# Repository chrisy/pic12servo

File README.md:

pic12servo
==========

This is a simple program to drive a hobby servo with a PIC12F683. It was
prepared using the MPLAB X IDE and the xc8 compiler.

The code sets up an analog-to-digital convertor input on pin 7 and
a PWM output on pin 5. It also sets up pulse outputs on pins 2 and 3
to allow us to measure the loop timing on an oscilloscope. The output
on pin 2 should be slow enough for a blinking LED.

The program loops reading the 10-bit value from the ADC and sets the
duty cycle of the PWM to a value derived from it.

The usable range for most servos requires a pulse length of between
about 1ms to 2ms (which represents the full range of motion for the
servo) with an overall pulse rate greater than 50Hz. This program
configures the PWM output to something close to 61Hz and calculates
the duty cycle value to correspond to a pulse of between about 1 and
2ms.

By hooking up a simple 10K ohm linear potentiometer wiper to pin 7,
with the pot ends across 0v and Vdd (the positive power to the PIC,
for example 5v) then the relative position of the pot will represent
the relative position of the servo motor across its full range.

Suitable hardware designs to facilitate this are in the hardware
directory.

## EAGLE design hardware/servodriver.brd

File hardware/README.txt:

The ServoDriver hardware
========================

servodriver.sch and servodriver.brd are Eagle diagrams.

servodriver.*.tap are G-Code CAM scripts generated using gcode-pcb.ulp.

Bill of Materials
=================

IC1		PIC12F683P (programmed, with 8 pin IC socket)
IC2		7805

R1		10K Pot
R2		Link
R3		620R
R4		620R

C1		0.1uF
C2		0.1uF
C3		0.1uF
C4		100uF electrolytic (25V or higher)
C5		10uF electrolytic (10V or higher)
C6		0.1uF

D1		1N4004

LED1	3mm red LED
LED2	3mm red LED

JP1		2-way Screw terminal
JP2		3-way 0.1" pitch pin header

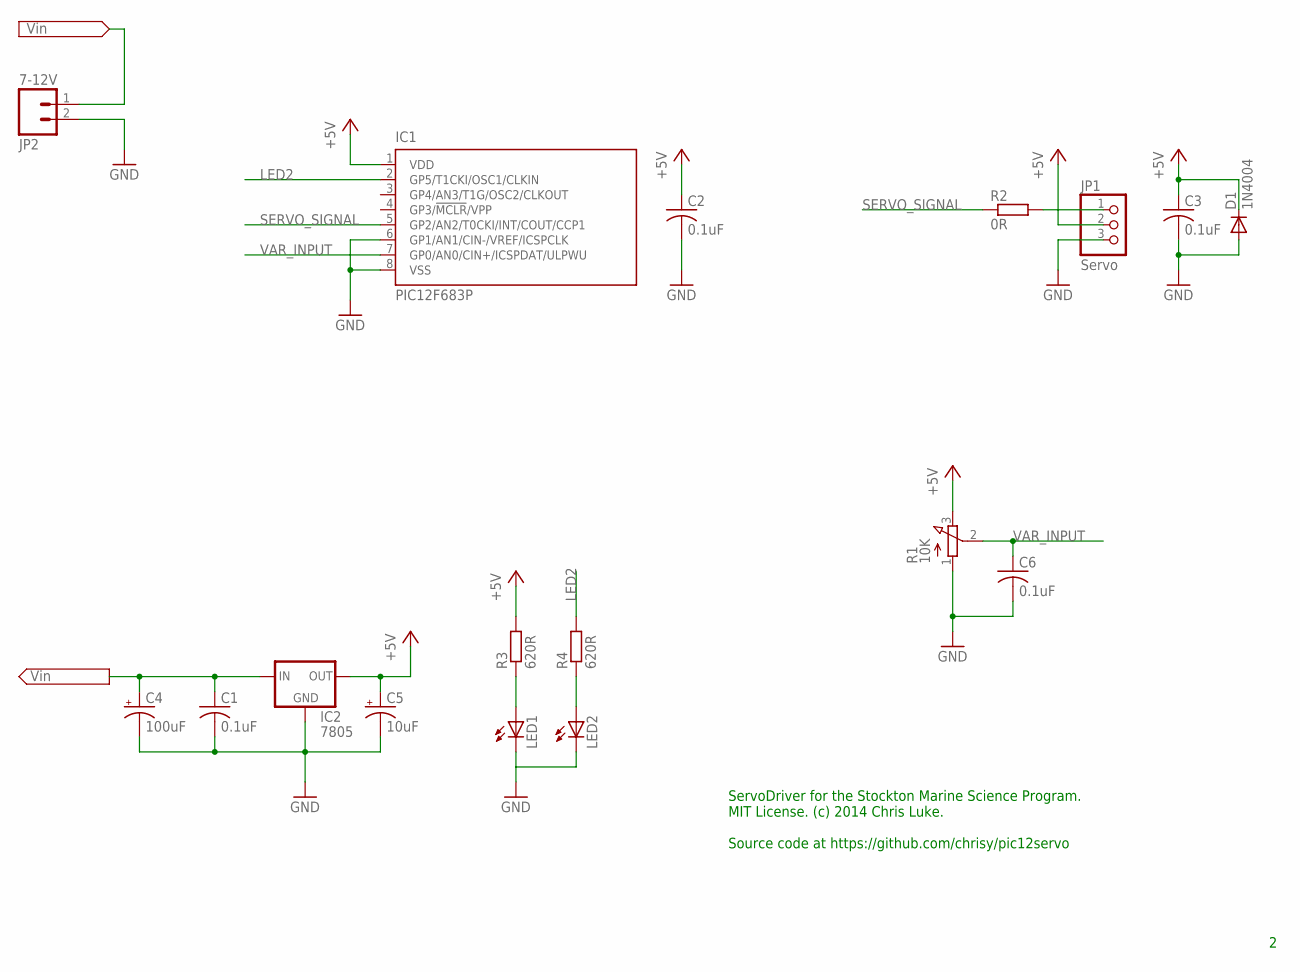
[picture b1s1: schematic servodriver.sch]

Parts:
C1, C2, C3, C6: 0.1uF; C025-025X050
C4: 100uF; E2,5-6
C5: 10uF; E2,5-6
D1: 1N4004; DO41-10
IC1: PIC12F683P; DIL8
IC2: 7805; 78XXL
JP1: Servo; 1X03
JP2: 7-12V; SCREWTERMINAL-3.5MM-2
LED1, LED2: LED3MM
R1: 10K; 3RP/1610N
R2: 0R; 0207/10
R3, R4: 620R; 0207/10

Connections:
+5V: C2.1, C3.1, C5.+, D1.C, IC1.1 (VDD), IC2.OUT, JP1.2, R1.3 (E), R3.2
GND: C1.2, C2.2, C3.2, C4.-, C5.-, C6.2, D1.A, IC1.6 (GP1/AN1/CIN-/VREF/ICSPCLK), IC1.8 (VSS), IC2.GND, JP1.3, JP2.2, LED1.K (C), LED2.K (C), R1.1 (A)
LED2: IC1.2 (GP5/T1CKI/OSC1/CLKIN), R4.2
unnamed: JP1.1, R2.2
unnamed: LED1.A, R3.1
unnamed: LED2.A, R4.1
SERVO_SIGNAL: IC1.5 (GP2/AN2/T0CKI/INT/COUT/CCP1), R2.1
VAR_INPUT: C6.1, IC1.7 (GP0/AN0/CIN+/ICSPDAT/ULPWU), R1.2 (S)
VIN: C1.1, C4.+, IC2.IN, JP2.1

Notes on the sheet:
ServoDriver for the Stockton Marine Science Program. MIT License. (c) 2014 Chris Luke. Source code at https://github.com/chrisy/pic12servo

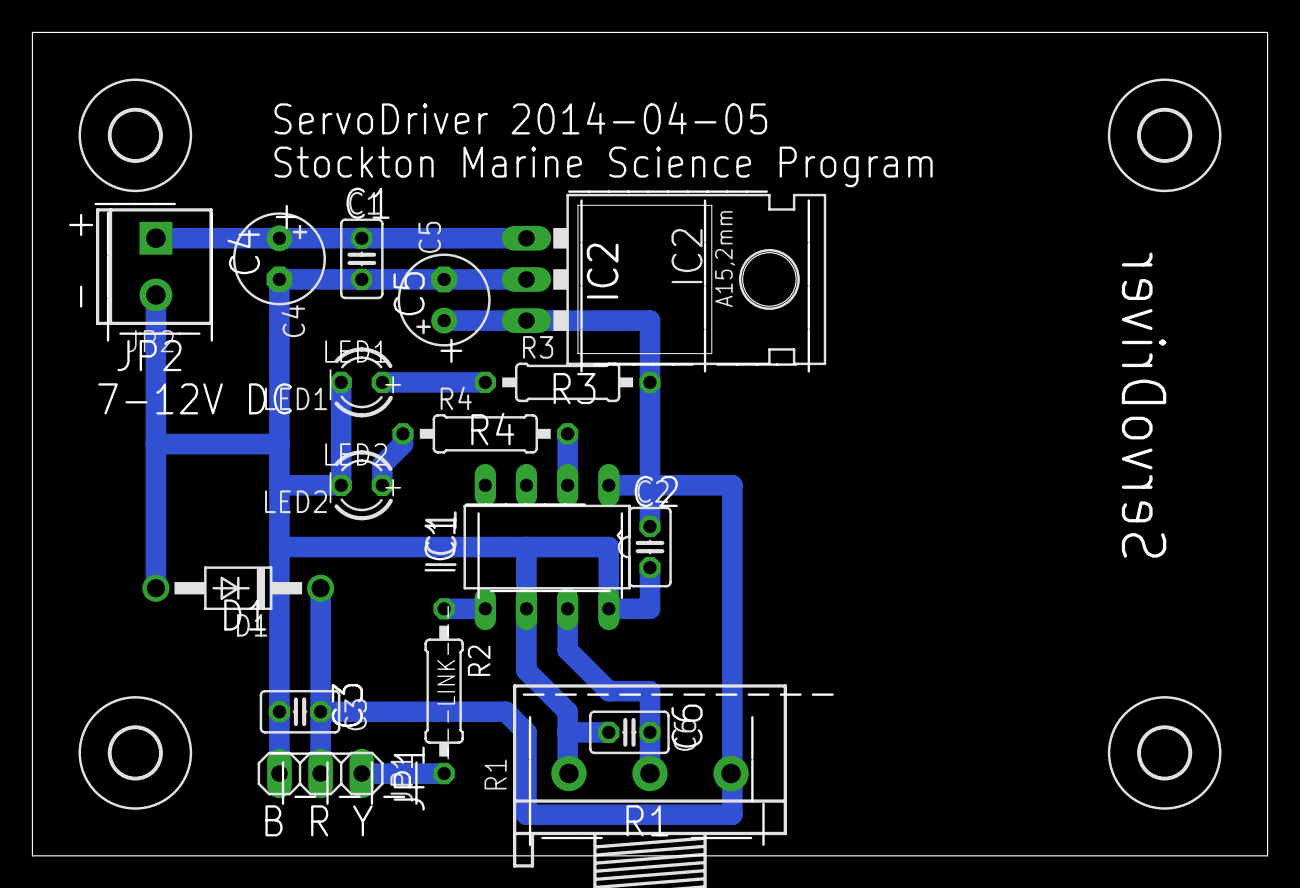
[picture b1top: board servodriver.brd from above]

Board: 2 copper layers, 76.2 x 50.8 mm, 21 parts (0 on the bottom side), 9 nets.

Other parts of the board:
U$1, U$2, U$3, U$4: 3,0

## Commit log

2014-03-03 Simple PIC12 servo driver; reads an ADC value and sets the PWM to it
2014-03-03 Add README
2014-03-03 Add MIT license
2014-03-14 Tweaks to make it work with most servos.
    In particular, it targets a specific pulse timing for the full
    range of the input signal. The useful range for most servos is
    about 1ms to 2ms of a pulse. The code calculates the desired
    pulse length and then converts this into the PWM timing
    necessary. This uses floating point for now, we may want to use
    integer math later for performance.
2014-04-05 Add a blinky LED output!
2014-04-05 Add the hardware schematic and board
2014-04-05 Add the CAM files
2014-04-06 Update the hardware files
    - Latest CNC files
    - Add images of the schematic and board layout
2014-04-06 Update the README, refactor headers, add a workaround
    - Add pulsed outputs description to README
    - Describe servo pulse requirements in README
    - Normalize line endings since we've been using both Windows and MacOS
    - Refactor some items into servo_driver.h for general hygiene
    - Work around a potential semantic issue when assigning a bit field from the results of the ! operator
2014-04-13 Update hardware details, including a BOM
2014-04-13 Refactor the hardware init, make the LED work
    Refactor hardware initialization into an init() function and tweak
    various things to make the LED output work. Not least, account for
    some annoying read-modify-write semantics on this PIC (which doesn't have an independent output latch register).
2014-04-19 add log files to .gitignore

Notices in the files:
parts and their libraries:
SparkFun-Connectors: Licensing: CC v3.0 Share-Alike You are welcome to use this library for commercial purposes.
